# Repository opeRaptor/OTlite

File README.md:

Obsolete Time Lite or O;TL for short, is the natural evolution of a previous project aiming to design the perfect desktop Nixie clock. 

 -Minimal design
 
 -Small form factor 
 
 -WiFi capable 
 
 -USB power 
 
 -Various atmospheric sensors. 

Reach out on Twitter: 
@SuprNova

Follow development on HackaDay.io:
https://hackaday.io/project/20439-obsolete-time-lite-a-minty-nixie-clock

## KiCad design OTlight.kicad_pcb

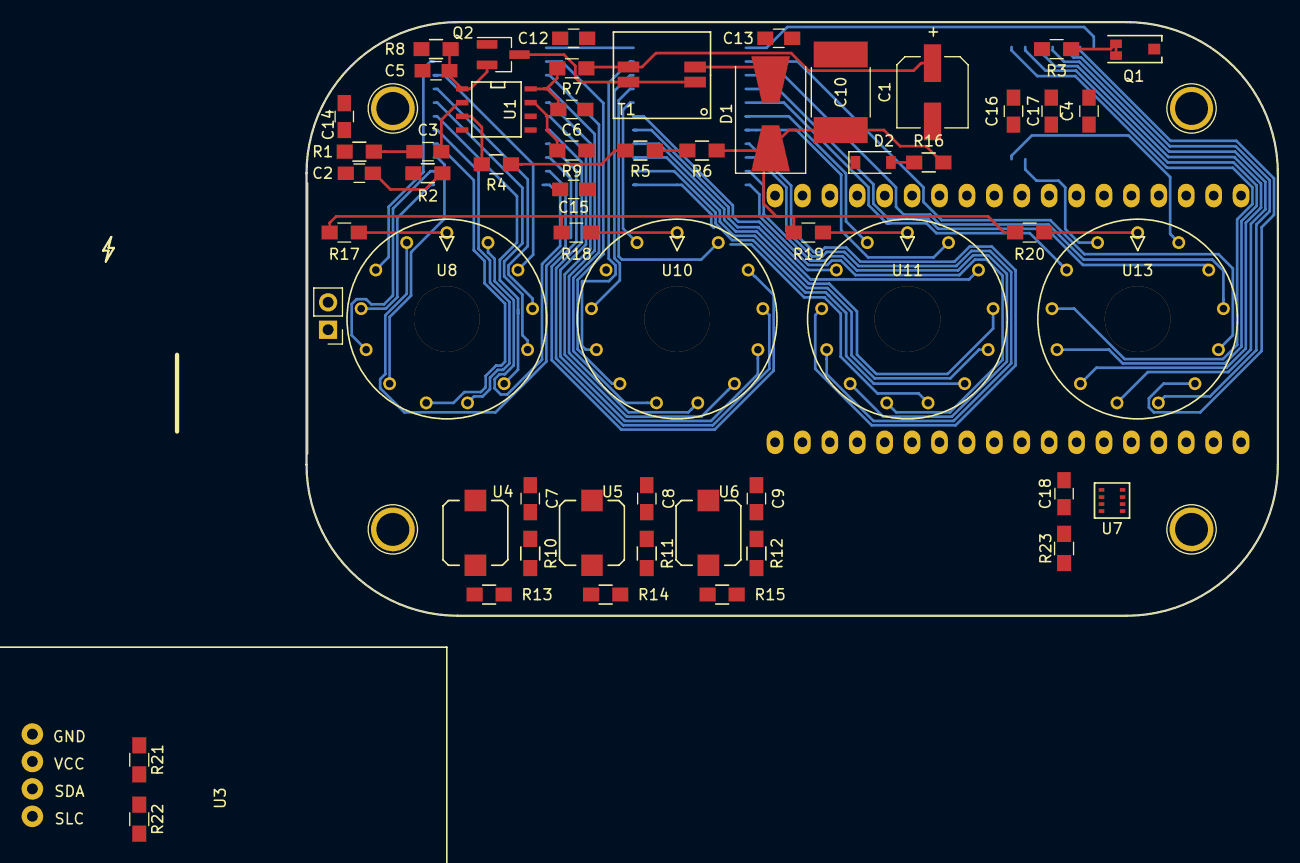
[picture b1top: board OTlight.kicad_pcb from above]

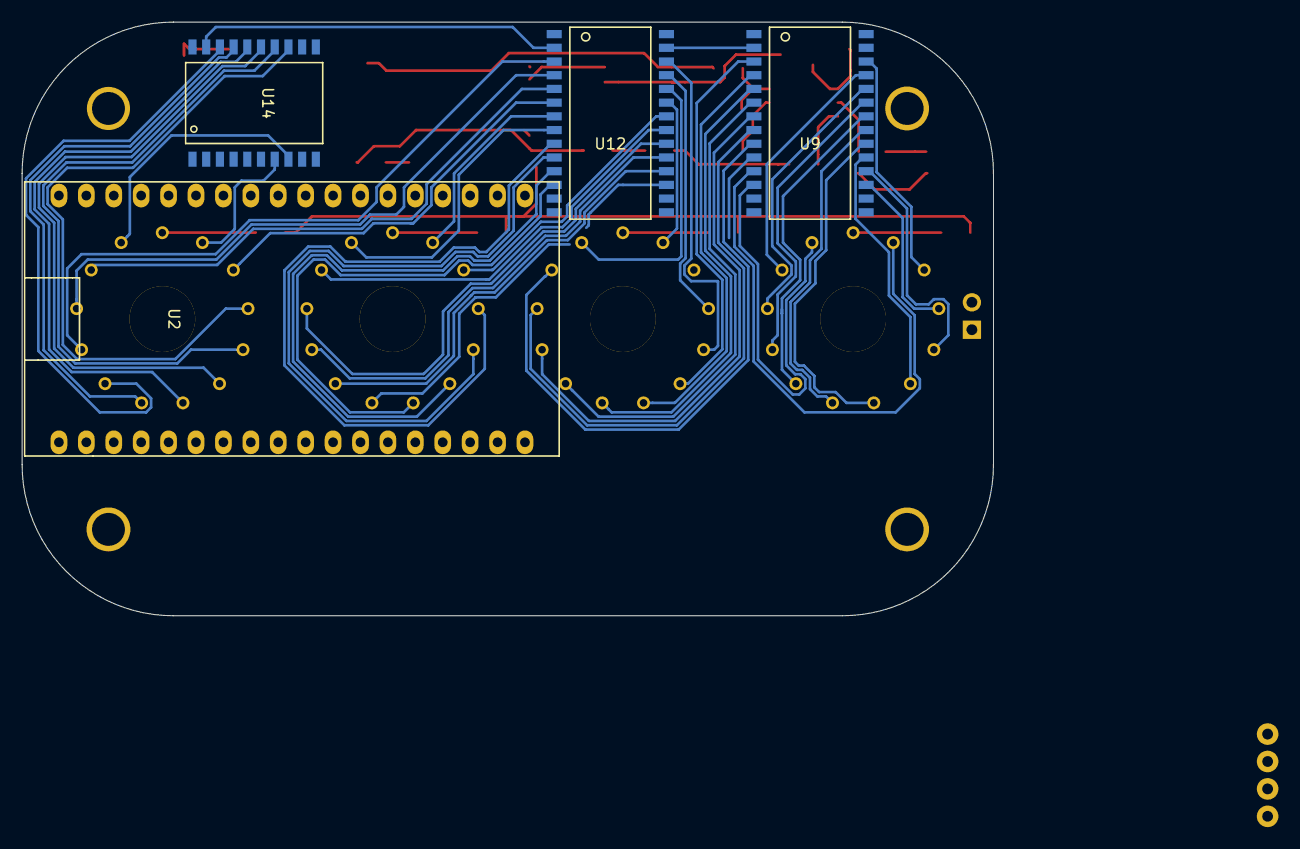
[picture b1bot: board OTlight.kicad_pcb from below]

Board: 2 copper layers, 90.0 x 55.0 mm, 60 parts (4 on the bottom side), 82 nets.

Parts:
C1: 220u; CP_Elec_6.3x7.7
C2: 0.001; C_0805_HandSoldering
C3, C6, C7, C8, C9, C18: 0.1u; C_0805_HandSoldering
C4: 10u; C_0805_HandSoldering
C5: 0.01u; C_0805_HandSoldering
C10: 1u; C_2220_HandSoldering
C12, C13, C14, C15, C16, C17: C_Small; C_0805_HandSoldering
D1: STPS4S200; D_SMB-SMC_Universal_Handsoldering
D2: D_Zener_Small_ALT; D_SOD-123
P1: CONN_01X02; Pin_Header_Straight_1x02_Pitch2.54mm
Q1: TEMT6000
Q2: RSR030N06TL; SOT-23_Handsoldering
R1: 1K; R_0805_HandSoldering
R2: 13K; R_0805_HandSoldering
R3, R10, R11, R12, R13, R14, R15, R16, R17, R18, R19, R20, R21, R22, R23: R_Small; R_0805_HandSoldering
R4: 1M; R_0805_HandSoldering
R5: 820K; R_0805_HandSoldering
R6: 24K; R_0805_HandSoldering
R7: 20; R_0805_HandSoldering
R8: 0.1; R_0805_HandSoldering
R9: 15K; R_0805_HandSoldering
T1: TRANSFO; CTX02-18714-R
U1: LM3478; SOIC-8-N
U2: ESP32; ESP32-OLED
U3: DS3231
U4, U5, U6: PushButton; SPEH120100
U7: bareBME280; BME280bare
U8, U10, U11, U13: IN-14; bearing-7mm
U9, U12: MAX6931; SW-28
U14: MAX6920; SW-20

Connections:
+3V3: C14.1, C15.1, C16.1, C18.2, Q1.1, R21.1, R22.1, R23.2, U3.2, U4.2, U5.2, U6.2, U7.2, U7.6, U7.8, U9.28, U12.28, U14.20
+5V: C1.1, C4.1, R7.1, T1.3
/CLK: U9.15, U12.15, U14.11
/HVout: C10.1, D1.1, P1.1, R6.1, R16.1, R17.1, R18.1, R19.1, R20.1
/LOAD: U9.16, U12.16, U14.12
GND: C1.2, C2.2, C4.2, C5.2, C6.2, C7.2, C8.2, C9.2, C10.2, C12.1, C13.1, C14.2, C15.2, C16.2, C17.1, C18.1, D2.1, P1.2, R1.2, R2.2, R3.2, R8.2, R9.1, R13.2, R14.2, R15.2, U1.4, U1.5, U3.1, U7.1, U7.7, U9.13, U9.14, U12.13, U12.14, U14.9, U14.10
unnamed: C2.1, R2.1, R4.2, U1.3
unnamed: C3.1, U1.2
unnamed: C3.2, R1.1
unnamed: C5.1, Q2.2, R8.1, U1.1
unnamed: C6.1, R7.2, U1.8
unnamed: C7.1, R10.1
unnamed: C8.1, R11.1
unnamed: C9.1, R12.1
unnamed: C12.2, C13.2, C17.2, D2.2, R16.2, U9.1, U12.1, U14.1
unnamed: D1.2, T1.2
unnamed: Q1.2, R3.1
unnamed: Q2.1, U1.6
unnamed: Q2.3, T1.1, T1.4
unnamed: R4.1, R5.2
unnamed: R5.1, R6.2
unnamed: R9.2, U1.7
unnamed: R10.2, R13.1, U4.1
unnamed: R11.2, R14.1, U5.1
unnamed: R12.2, R15.1, U6.1
unnamed: R17.2, U8.1
unnamed: R18.2, U10.1
unnamed: R19.2, U11.1
unnamed: R20.2, U13.1
unnamed: R21.2, U3.3, U7.3
unnamed: R22.2, U3.4, U7.4
unnamed: R23.1, U7.5
unnamed: U8.2, U9.12
unnamed: U8.3, U9.25
unnamed: U8.4, U9.24
unnamed: U8.5, U9.23
unnamed: U8.6, U9.22
unnamed: U8.7, U9.21
unnamed: U8.8, U9.20
unnamed: U8.9, U9.19
unnamed: U8.10, U9.18
unnamed: U8.11, U9.17
unnamed: U8.12, U9.26
unnamed: U8.13, U9.11
unnamed: U10.2, U12.24
unnamed: U9.9, U10.3
unnamed: U9.8, U10.4
unnamed: U9.7, U10.5
unnamed: U9.6, U10.6
unnamed: U9.5, U10.7
unnamed: U9.4, U10.8
unnamed: U9.3, U10.9
unnamed: U10.10, U12.26
unnamed: U10.11, U12.25
unnamed: U9.10, U10.12
unnamed: U10.13, U12.23
unnamed: U11.2, U12.8
unnamed: U11.3, U12.21
unnamed: U11.4, U12.20
unnamed: U11.5, U12.19
unnamed: U11.6, U12.18
unnamed: U11.7, U12.17
unnamed: U11.8, U12.12
unnamed: U11.9, U12.11
unnamed: U11.10, U12.10
unnamed: U11.11, U12.9
unnamed: U11.12, U12.22
unnamed: U11.13, U12.7
unnamed: U12.2, U14.19
unnamed: U12.3, U13.5
unnamed: U12.4, U13.4
unnamed: U12.5, U13.3
unnamed: U12.6, U13.12
unnamed: U9.2, U12.27
unnamed: U13.2, U14.8
unnamed: U13.6, U14.18
unnamed: U13.7, U14.17
unnamed: U13.8, U14.16
unnamed: U13.9, U14.15
unnamed: U13.10, U14.14
unnamed: U13.11, U14.13
unnamed: U13.13, U14.7

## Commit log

2017-01-18 Initial Push~
2017-01-20 Everything Connected
2017-01-21 Touch up + added I2C Pullups
2017-01-21 Schematic Update
    changelog:
    - Linked labels
    - Added MAXIM6920 to rout the dot
    - Set values to passive components
    - Cosmetic changes
2017-01-22 Fixes + PCB created
    Fixed buttons generated PCB+ started rough laying
2017-03-08 Components fitted
    Everything fits!
2017-03-09 PSU on board organised
2017-03-12 ShiftRegisters + Nixies Routed
    ESP in place also
2017-03-15 PSU rooted
    Needs clean up and RTC+Barometer fitted
2017-03-16 Finished routing PCB
2017-03-18 Clean up
    We are getting there!
2017-03-22 Biribiri silkscreen, clean up, where are the GND vias?
2017-03-25 Separated all the pads from the vias... sigh
2017-03-25 Misakaimouto Silk + miniBiri stitch
2017-03-25 Added Edgecut on top of the Altoids silkscreen
2017-03-25 Board size to fit Altoids+ decoupling caps
    NOTHING IS WHERE IT SHOULD BE
    EVERYTHING IS WRONG
    I AM GOING TO BED!
2017-03-25 Errr... as below but this time I saved first.
2017-03-26 SourceTree test
2017-03-26 Updated PCB and footprints - Changed footprints for angled pins SMD package - Repositioned holes - Locked Altoids shaped outline, holes, tubes and modules - Changed R3 for resistor package (was 0805 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
2017-03-26 Updated footprints meant reroute No unconnected traces, silk adjusted.
2017-04-05 Software Test of RTC + ATH Wire.pins(0,2); //SDA and SCL
2017-04-05 Renamed components on schematics for more sensible name Also changed diode orientation and BME280 pinout
2017-04-06 I2C footprint, silk and diode adjustments
2017-04-06 Final silk adjustment. Ready for fab?
2017-04-14 Changed QR code for non inverted colours Moved Q2 silkscreen Changed Biri-Biri via for 0.3mm
2017-04-17 Software started - all modules tested Test 1 just test the tubes Test 2 is a draft of all modules somehow working + some features
2017-04-19 ASS network test with NTP
2017-04-19 Reverted changes to test 2
2017-04-19 Reverted Test 2... This time I mean it.
2017-04-22 Displays number of Likes on HaD (good example of HTTP GET)
2017-04-22 Improved Provisional test 2 Improved the transition function, commented the functions, general cleanup
2017-04-22 Draft of Chronometer
2017-04-23 Final cleanup of most basic functions Chronometer commented out Some glitches are remaining for the Transition function
2017-04-23 Base software for the clock, project format is Platform IO
2017-04-23 Updated tube brightness control
2017-05-02 Updates MQTT every 10min for battery test.
2017-05-15 Rev2 of the board Everything fits and is connected~
2017-05-18 Cleanup started
2017-05-19 Added edge cut and M3 mounting holes
2018-01-20 The start of bearing upgrade
2018-01-20 Realigned tubes with bearings, now the tubes are perfectly centered on both x and y axis
2018-01-27 Everything in place with bearings sockets.
2018-02-22 Add files via upload
    Added Test nixie bearing files, just a quick PCB for testing various settings on the tube sockets with bearings.
    Note the associated footprints are not in Bamboulib, since I had to create about 20 abominations to create this monstruosity, if the tests are successful I will upload the appropriate libraries
